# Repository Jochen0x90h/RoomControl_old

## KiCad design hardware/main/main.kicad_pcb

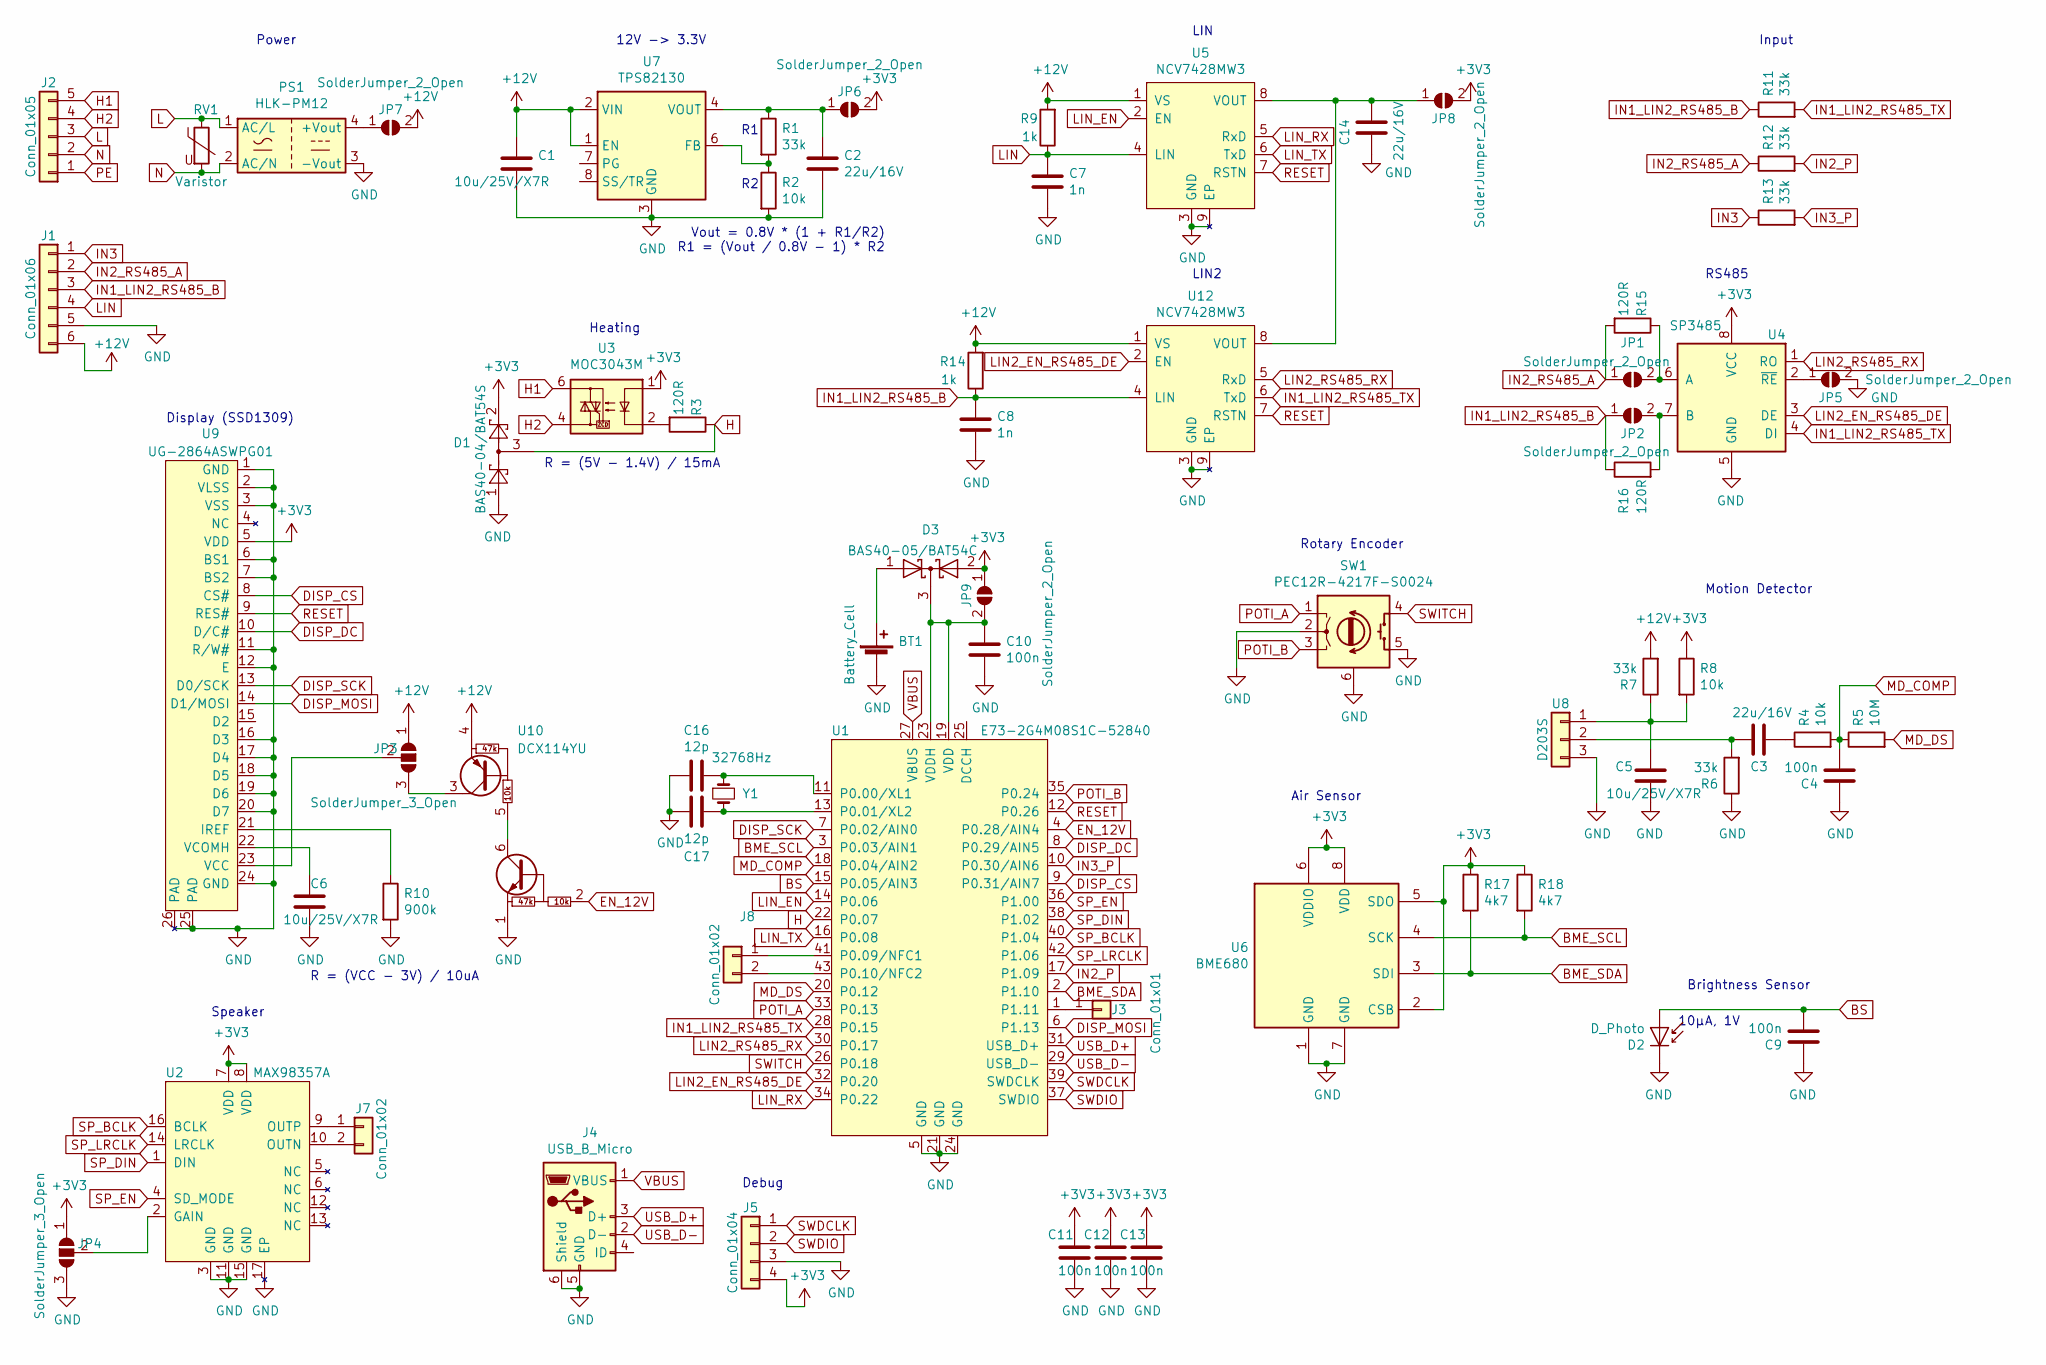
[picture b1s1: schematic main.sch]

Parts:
BT1: Battery_Cell; Battery_2032
C1, C5, C6: 10u/25V/X7R; C_1206_3216Metric
C2, C3, C14: 22u/16V; C_0805_2012Metric
C4, C9, C10, C11, C12, C13: 100n; C_0603_1608Metric
C7, C8: 1n; C_0603_1608Metric
C16, C17: 12p; C_0603_1608Metric
D1: BAS40-04/BAT54S; SOT-23
D2: D_Photo; DiodeHoles
D3: BAS40-05/BAT54C; SOT-23
J1: Conn_01x06; Wago_236-406
J2: Conn_01x05; Wago_236-405
J3: Conn_01x01; Pad
J4: USB_B_Micro; USB_Micro-B
J5: Conn_01x04; PinHeader_1x04_P2.54mm_Vertical
J7: Conn_01x02; PinHeader_1x02_P2.54mm_Vertical
J8: Conn_01x02; PinHeader_1x02_P2.00mm_Vertical
JP1, JP2, JP5, JP6, JP7, JP8, JP9: SolderJumper_2_Open; Jumper2
JP3, JP4: SolderJumper_3_Open; Jumper3
PS1: HLK-PM12; HiLink_HLK-PMxx
R1, R6, R7: 33k; R_0603_1608Metric
R2, R4, R8: 10k; R_0603_1608Metric
R3, R15, R16: 120R; R_1206_3216Metric
R5: 10M; R_0603_1608Metric
R9, R14: 1k; R_1206_3216Metric
R10: 900k; R_0603_1608Metric
R11, R12, R13: 33k; R_1206_3216Metric
R17, R18: 4k7; R_0603_1608Metric
RV1: Varistor; S10K275
SW1: PEC12R-4217F-S0024; Bourns_PEC12R
U1: E73-2G4M08S1C-52840
U2: MAX98357A; TQFN-16-1EP_3x3mm_P0.5mm_EP1.23x1.23mm
U3: MOC3043M; On_MOC3043
U4: SP3485; SOIC-8_3.9x4.9mm_P1.27mm
U5, U12: NCV7428MW3; On_NCV7428MW
U6: BME680; Bosch_BME680
U7: TPS82130; Texas_TPS82130
U8: D203S
U9: UG-2864ASWPG01; Connector-Flat-24_P0.5mm
U10: DCX114YU; SOT-363_SC-70-6
Y1: 32768Hz; Crystal_DS26_D2.0mm_L6.0mm_Vertical

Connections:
+3V3: C11.2, C12.2, C13.2, D1.2, D3.2 (A), J5.4, JP4.1 (A), JP6.2 (B), JP8.2 (B), JP9.1 (A), R8.1, R17.1, R18.1, U2.7 (VDD), U2.8 (VDD), U3.1, U4.8 (VCC), U6.2 (CSB), U6.5 (SDO), U6.6 (VDDIO), U6.8 (VDD), U9.5 (VDD)
+12V: C1.1, J1.6, JP3.1 (A), JP7.2 (B), R7.2, R9.2, R14.2, U5.1 (VS), U7.1 (EN), U7.2 (VIN), U10.4 (C2), U12.1 (VS)
BME_SCL: R18.2, U1.3 (P0.03/AIN1), U6.4 (SCK)
BME_SDA: R17.2, U1.2 (P1.10), U6.3 (SDI)
BS: C9.2, D2.2 (A), U1.15 (P0.05/AIN3)
DISP_CS: U1.9 (P0.31/AIN7), U9.8 (CS#)
DISP_DC: U1.8 (P0.29/AIN5), U9.10 (D/C#)
DISP_MOSI: U1.6 (P1.13), U9.14 (D1/MOSI)
DISP_SCK: U1.7 (P0.02/AIN0), U9.13 (D0/SCK)
EN_12V: U1.4 (P0.28/AIN4), U10.2 (B1)
GND: BT1.2 (-), C1.2, C2.2, C4.1, C5.2, C6.2, C7.2, C8.2, C9.1, C10.2, C11.1, C12.1, C13.1, C14.1, C16.2, C17.2, D1.1, D2.1 (K), J1.5, J4.5 (GND), J4.6 (Shield), J5.3, JP4.3 (B), JP5.2 (B), PS1.3 (-Vout), R2.2, R6.1, R10.2, SW1.2 (C), SW1.5 (S2), SW1.6 (SH), U1.5 (GND), U1.21 (GND), U1.24 (GND), U2.3 (GND), U2.11 (GND), U2.15 (GND), U2.17 (EP), U4.5 (GND), U5.3 (GND), U5.9 (EP), U6.1 (GND), U6.7 (GND), U7.3 (GND), U7.9 (GND), U8.3, U9.1 (GND), U9.2 (VLSS), U9.3 (VSS), U9.6 (BS1), U9.7 (BS2), U9.11 (R/W#), U9.12 (E), U9.16 (D3), U9.17 (D4), U9.18 (D5), U9.19 (D6), U9.20 (D7), U9.24 (GND), U9.25 (PAD), U9.26 (PAD), U10.1 (E1), U12.3 (GND), U12.9 (EP)
H: D1.3, R3.1, U1.22 (P0.07)
H1: J2.5, U3.6
H2: J2.4, U3.4
IN1_LIN2_RS485_B: C8.1, J1.3, JP2.1 (A), R11.1, R14.1, R16.1, U12.4 (LIN)
IN1_LIN2_RS485_TX: R11.2, U1.28 (P0.15), U4.4 (DI), U12.6 (TxD)
IN2_P: R12.2, U1.17 (P1.09)
IN2_RS485_A: J1.2, JP1.1 (A), R12.1, R15.2
IN3: J1.1, R13.1
IN3_P: R13.2, U1.10 (P0.30/AIN6)
L: J2.3, PS1.1 (AC/L), RV1.1
LIN: C7.1, J1.4, R9.1, U5.4 (LIN)
LIN2_EN_RS485_DE: U1.32 (P0.20), U4.3 (DE), U12.2 (EN)
LIN2_RS485_RX: U1.30 (P0.17), U4.1 (RO), U12.5 (RxD)
LIN_EN: U1.14 (P0.06), U5.2 (EN)
LIN_RX: U1.34 (P0.22), U5.5 (RxD)
LIN_TX: U1.16 (P0.08), U5.6 (TxD)
MD_COMP: C4.2, R4.2, R5.1, U1.18 (P0.04/AIN2)
MD_DS: R5.2, U1.20 (P0.12)
N: J2.2, PS1.2 (AC/N), RV1.2
unnamed: BT1.1 (+), D3.1 (A)
unnamed: C2.1, JP6.1 (A), R1.1, U7.4 (VOUT), U7.5 (VOUT)
unnamed: C3.1, R4.1
unnamed: C3.2, R6.2, U8.2
unnamed: C5.1, R7.1, R8.2, U8.1
unnamed: C6.1, U9.22 (VCOMH)
unnamed: C10.1, D3.3 (K), JP9.2 (B), U1.19 (VDD), U1.23 (VDDH)
unnamed: C14.2, JP8.1 (A), U5.8 (VOUT), U12.8 (VOUT)
unnamed: C16.1, U1.11 (P0.00/XL1), Y1.1
unnamed: C17.1, U1.13 (P0.01/XL2), Y1.2
unnamed: J3.1, U1.1 (P1.11)
unnamed: J7.1, U2.9 (OUTP)
unnamed: J7.2, U2.10 (OUTN)
unnamed: J8.1, U1.41 (P0.09/NFC1)
unnamed: J8.2, U1.43 (P0.10/NFC2)
unnamed: JP1.2 (B), R15.1, U4.6 (A)
unnamed: JP2.2 (B), R16.2, U4.7 (B)
unnamed: JP3.2 (C), U9.23 (VCC)
unnamed: JP3.3 (B), U10.3 (C2)
unnamed: JP4.2 (C), U2.2 (GAIN)
unnamed: JP5.1 (A), U4.2 (~RE~)
unnamed: JP7.1 (A), PS1.4 (+Vout)
unnamed: R1.2, R2.1, U7.6 (FB)
unnamed: R3.2, U3.2
unnamed: R10.1, U9.21 (IREF)
unnamed: U10.5 (B2), U10.6 (C1)
PE: J2.1
POTI_A: SW1.1 (A), U1.33 (P0.13)
POTI_B: SW1.3 (B), U1.35 (P0.24)
RESET: U1.12 (P0.26), U5.7 (RSTN), U9.9 (RES#), U12.7 (RSTN)
SP_BCLK: U1.40 (P1.04), U2.16 (BCLK)
SP_DIN: U1.38 (P1.02), U2.1 (DIN)
SP_EN: U1.36 (P1.00), U2.4 (SD_MODE)
SP_LRCLK: U1.42 (P1.06), U2.14 (LRCLK)
SWDCLK: J5.1, U1.39 (SWDCLK)
SWDIO: J5.2, U1.37 (SWDIO)
SWITCH: SW1.4 (S1), U1.26 (P0.18)
USB_D+: J4.3 (D+), U1.31 (USB_D+)
USB_D-: J4.2 (D-), U1.29 (USB_D-)
VBUS: J4.1 (VBUS), U1.27 (VBUS)

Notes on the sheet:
Vout = 0.8V * (1 + R1/R2) R1 = (Vout / 0.8V - 1) * R2
R = (VCC - 3V) / 10uA
Motion Detector
Display (SSD1309)
Speaker
Brightness Sensor
Input
LIN
RS485
12V -> 3.3V
Rotary Encoder
Air Sensor
Power
Heating
10µA, 1V
R = (5V - 1.4V) / 15mA
LIN2
Debug

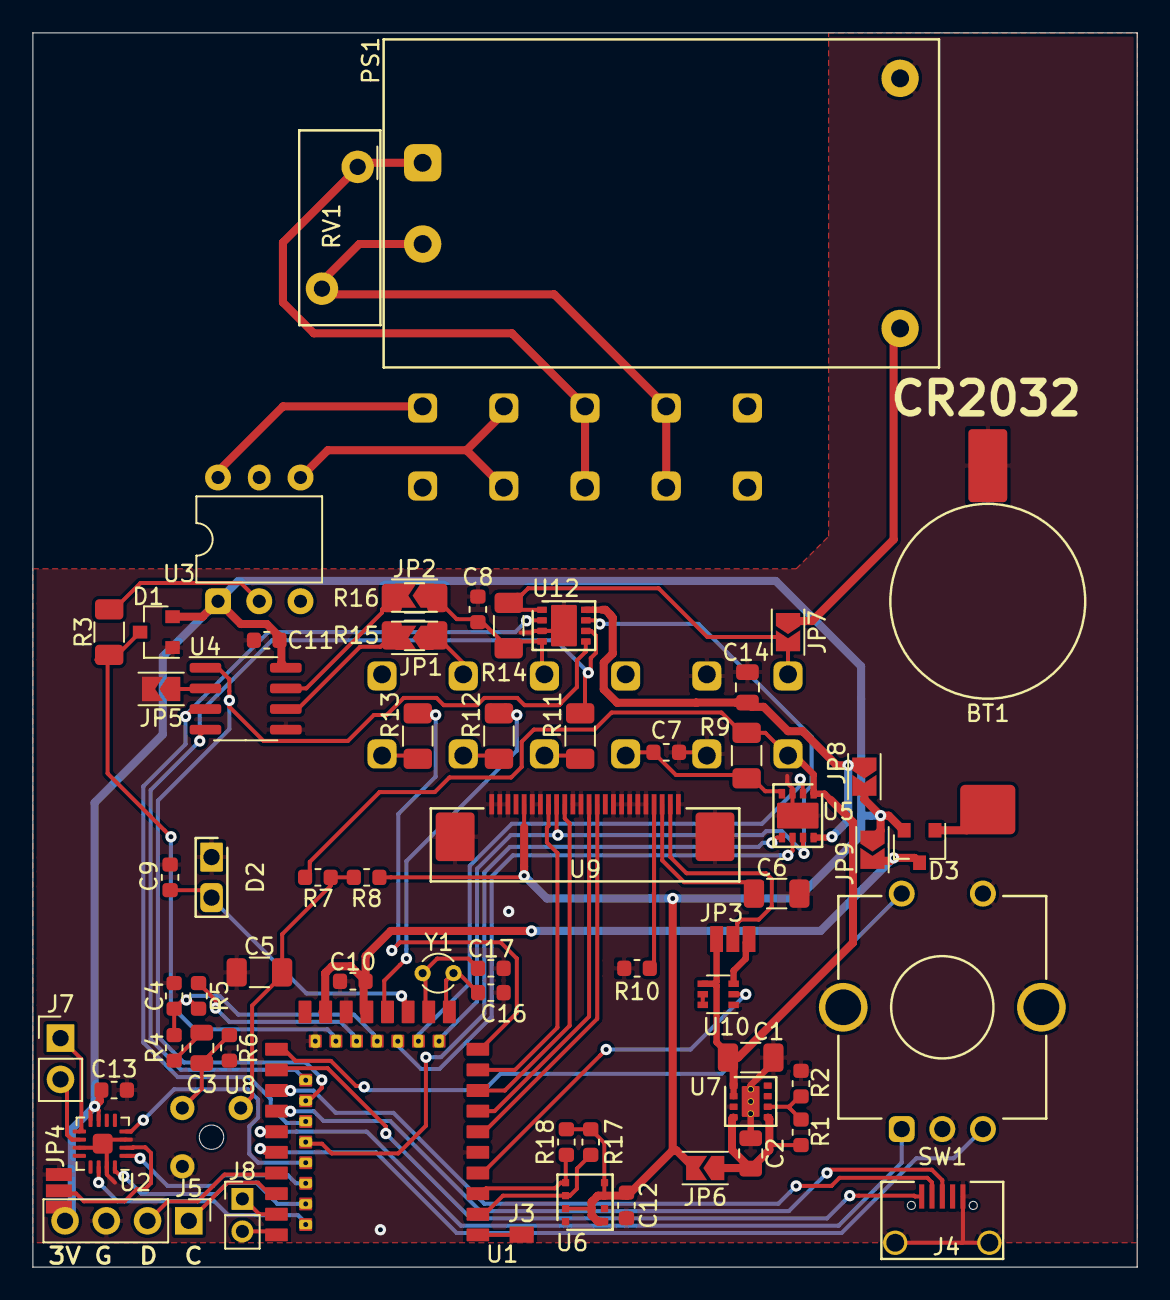
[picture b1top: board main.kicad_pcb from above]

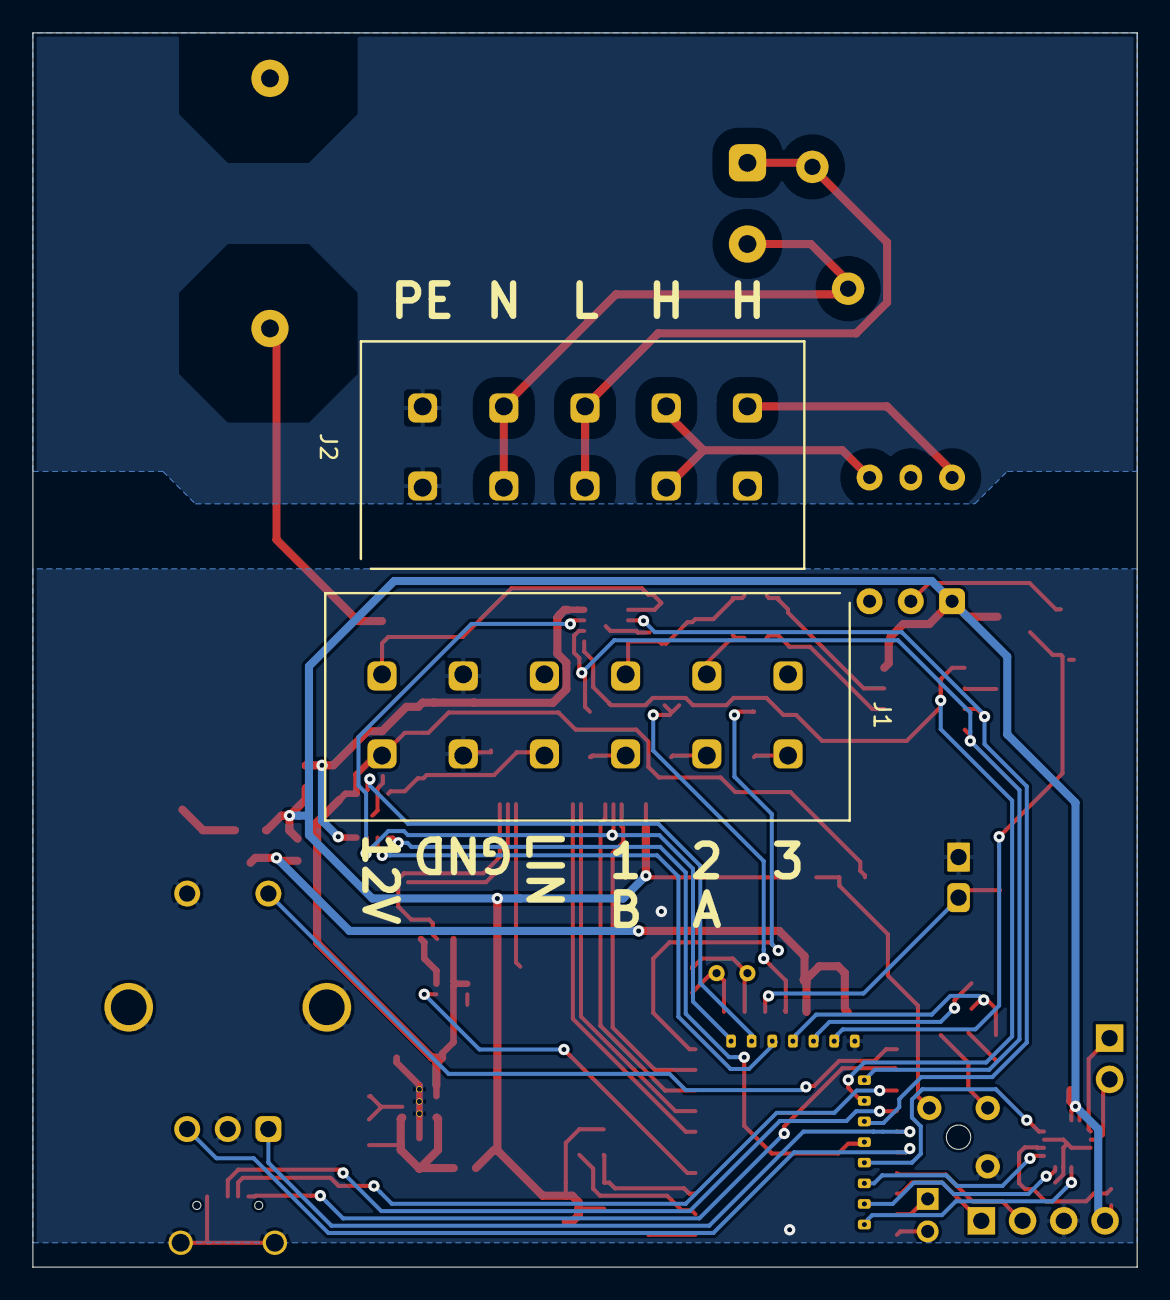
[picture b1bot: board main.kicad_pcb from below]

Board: 2 copper layers, 68.0 x 76.0 mm, 69 parts (2 on the bottom side), 69 nets.

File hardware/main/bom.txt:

1 120R 1206
1 1k 1206
3 10k 0603
3 33k 0603
1 900k 0603
1 10M 0603
2 12p 0603
7 100n 0603
3 10u/25V/X7R 1206
3 22u/16V 0805
1 E73-2G4M08S1C-52840
1 NCV7428MW3 (On lin driver)
1 MOC3043M (On optotriac)
1 MAX98357A (Maxim audio driver)
1 BME680 (Bosch air sensor)
1 PEC12R-4217F-S0024 (Bourns poti)
1 IRA-S410ST01 (Murata pir sensor)
1 IML-0685 (lens)
1 SFH 203 P (Osram photodiode)
1 BAS40-05/BAT54C
1 CR2032 holder
1 32768Hz (crystal)
1 S10K275 (varistor)
1 Wago 236-405
1 Wago 236-406
1 USB_B_Micro
1 24 pin display connector
1 TPS82130 (Texas buck converter 17V)
1 HLK-PM12 (AC/DC converter)
1 CDS-25148-L100 (Cui Devices speaker)

[inputs]
3 33k 1206

[ledstrip]
2 120R 1206
1 SP3485 (rs485 driver)
1 100n 0603

[optional]
1 1k 1206
2 4k7 0603
1 DCX114YU
1 BAS40-04/BAT54S
1 NCV7428MW3 (On lin driver)

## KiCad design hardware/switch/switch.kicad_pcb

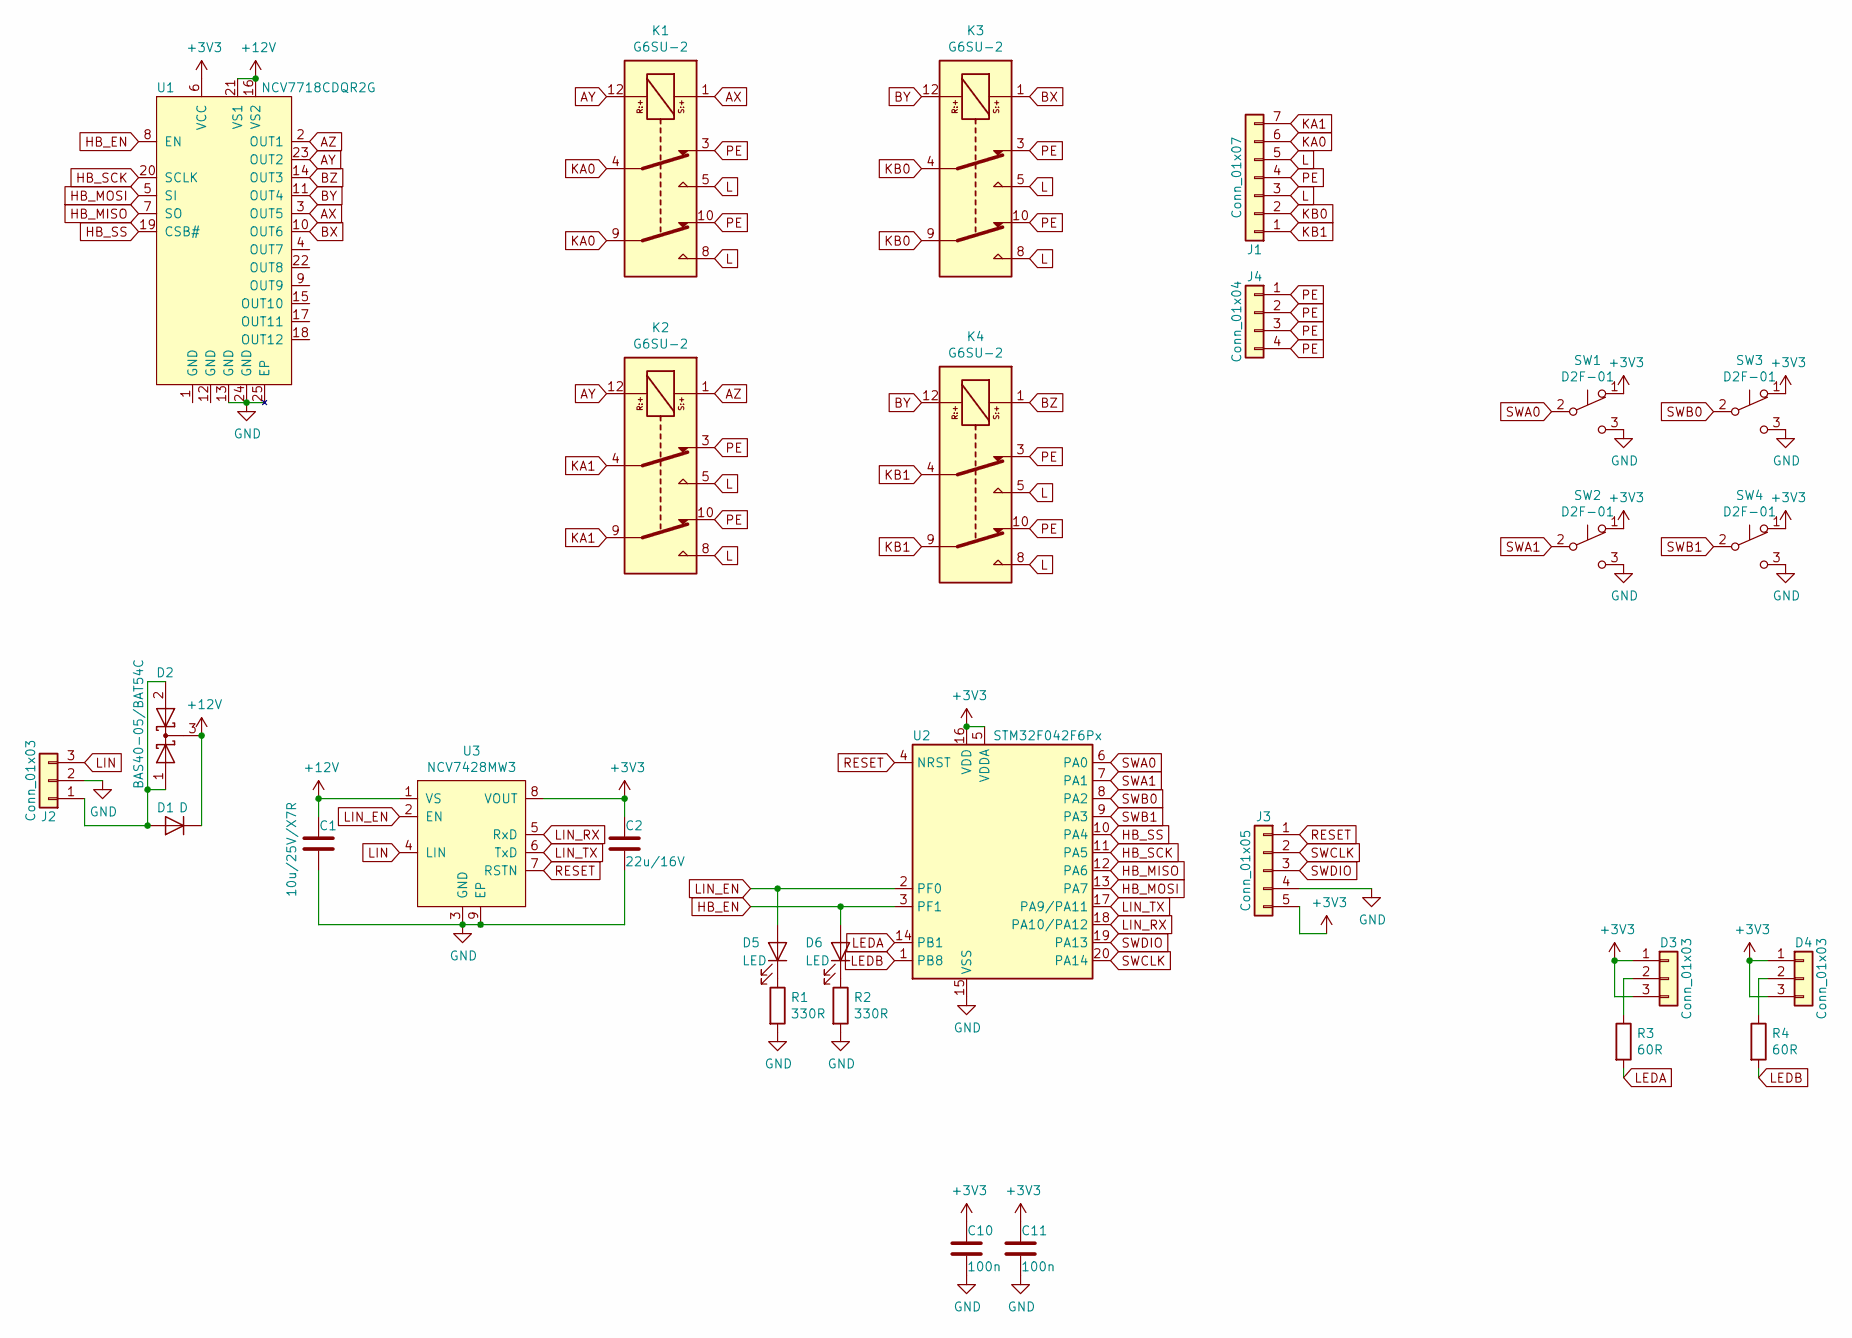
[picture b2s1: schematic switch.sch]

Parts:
C1: 10u/25V/X7R; C_1206_3216Metric
C2: 22u/16V; C_0805_2012Metric
C10, C11: 100n; C_0603_1608Metric
D1: D; D_1206_3216Metric_Castellated
D2: BAS40-05/BAT54C; SOT-23
D3, D4: Conn_01x03; DiodeHoles3
D5, D6: LED; LED_0805_2012Metric_Castellated
J1: Conn_01x07; Wago_236-407
J2: Conn_01x03; Wago_236-403
J3: Conn_01x05; PinHeader_1x05_P2.54mm_Vertical
J4: Conn_01x04; Switch_Mount
K1, K2, K3, K4: G6SU-2; Omron_G6SU-2
R1, R2: 330R; R_0603_1608Metric
R3, R4: 60R; R_0603_1608Metric
SW1, SW2, SW3, SW4: D2F-01; Omron_D2F-01
U1: NCV7718CDQR2G; On_NCV77xx
U2: STM32F042F6Px; STM32F042F6
U3: NCV7428MW3; On_NCV7428MW

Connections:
+3V3: C2.1, C10.1, C11.1, D3.1, D3.3, D4.1, D4.3, J3.5, SW1.1 (A), SW2.1 (A), SW3.1 (A), SW4.1 (A), U1.6 (VCC), U2.5 (VDDA), U2.16 (VDD), U3.8 (VOUT)
+12V: C1.1, D1.1 (K), D2.3 (K), U1.16 (VS2), U1.21 (VS1), U3.1 (VS)
AX: K1.1, U1.3 (OUT5)
AY: K1.12, K2.12, U1.23 (OUT2)
AZ: K2.1, U1.2 (OUT1)
BX: K3.1, U1.10 (OUT6)
BY: K3.12, K4.12, U1.11 (OUT4)
BZ: K4.1, U1.14 (OUT3)
GND: C1.2, C2.2, C10.2, C11.2, J2.2, J3.4, R1.2, R2.2, SW1.3 (C), SW2.3 (C), SW3.3 (C), SW4.3 (C), U1.13 (GND), U1.24 (GND), U1.25 (EP), U2.15 (VSS), U3.3 (GND), U3.9 (EP)
HB_EN: D6.2 (A), U1.8 (EN), U2.3 (PF1)
HB_MISO: U1.7 (SO), U2.12 (PA6)
HB_MOSI: U1.5 (SI), U2.13 (PA7)
HB_SCK: U1.20 (SCLK), U2.11 (PA5)
HB_SS: U1.19 (CSB#), U2.10 (PA4)
KA0: J1.6, K1.4, K1.9
KA1: J1.7, K2.4, K2.9
KB0: J1.2, K3.4, K3.9
KB1: J1.1, K4.4, K4.9
L: J1.3, J1.5, K1.5, K1.8, K2.5, K2.8, K3.5, K3.8, K4.5, K4.8
LEDA: R3.2, U2.14 (PB1)
LEDB: R4.2, U2.1 (PB8)
LIN: J2.3, U3.4 (LIN)
LIN_EN: D5.2 (A), U2.2 (PF0), U3.2 (EN)
LIN_RX: U2.18 (PA10/PA12), U3.5 (RxD)
LIN_TX: U2.17 (PA9/PA11), U3.6 (TxD)
unnamed: D1.2 (A), D2.1 (A), D2.2 (A), J2.1
unnamed: D3.2, R3.1
unnamed: D4.2, R4.1
unnamed: D5.1 (K), R1.1
unnamed: D6.1 (K), R2.1
PE: J1.4, J4.1, J4.2, J4.3, J4.4, K1.3, K1.10, K2.3, K2.10, K3.3, K3.10, K4.3, K4.10
RESET: J3.1, U2.4 (NRST), U3.7 (RSTN)
SWA0: SW1.2 (B), U2.6 (PA0)
SWA1: SW2.2 (B), U2.7 (PA1)
SWB0: SW3.2 (B), U2.8 (PA2)
SWB1: SW4.2 (B), U2.9 (PA3)
SWCLK: J3.2, U2.20 (PA14)
SWDIO: J3.3, U2.19 (PA13)

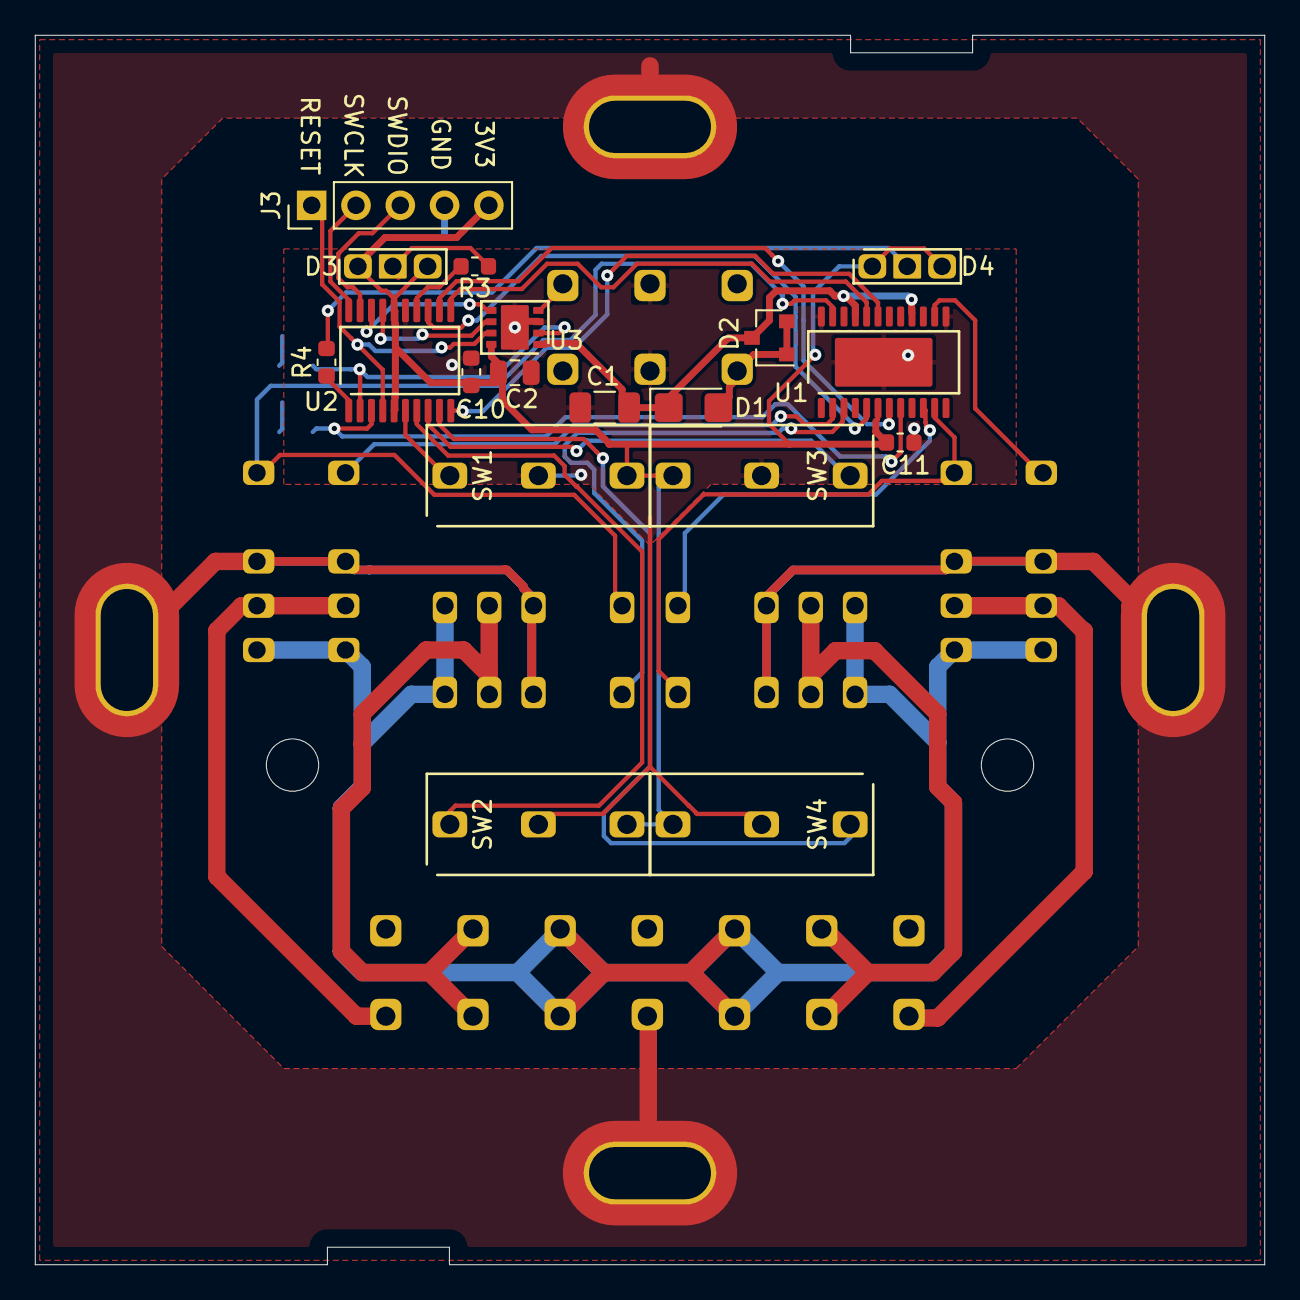
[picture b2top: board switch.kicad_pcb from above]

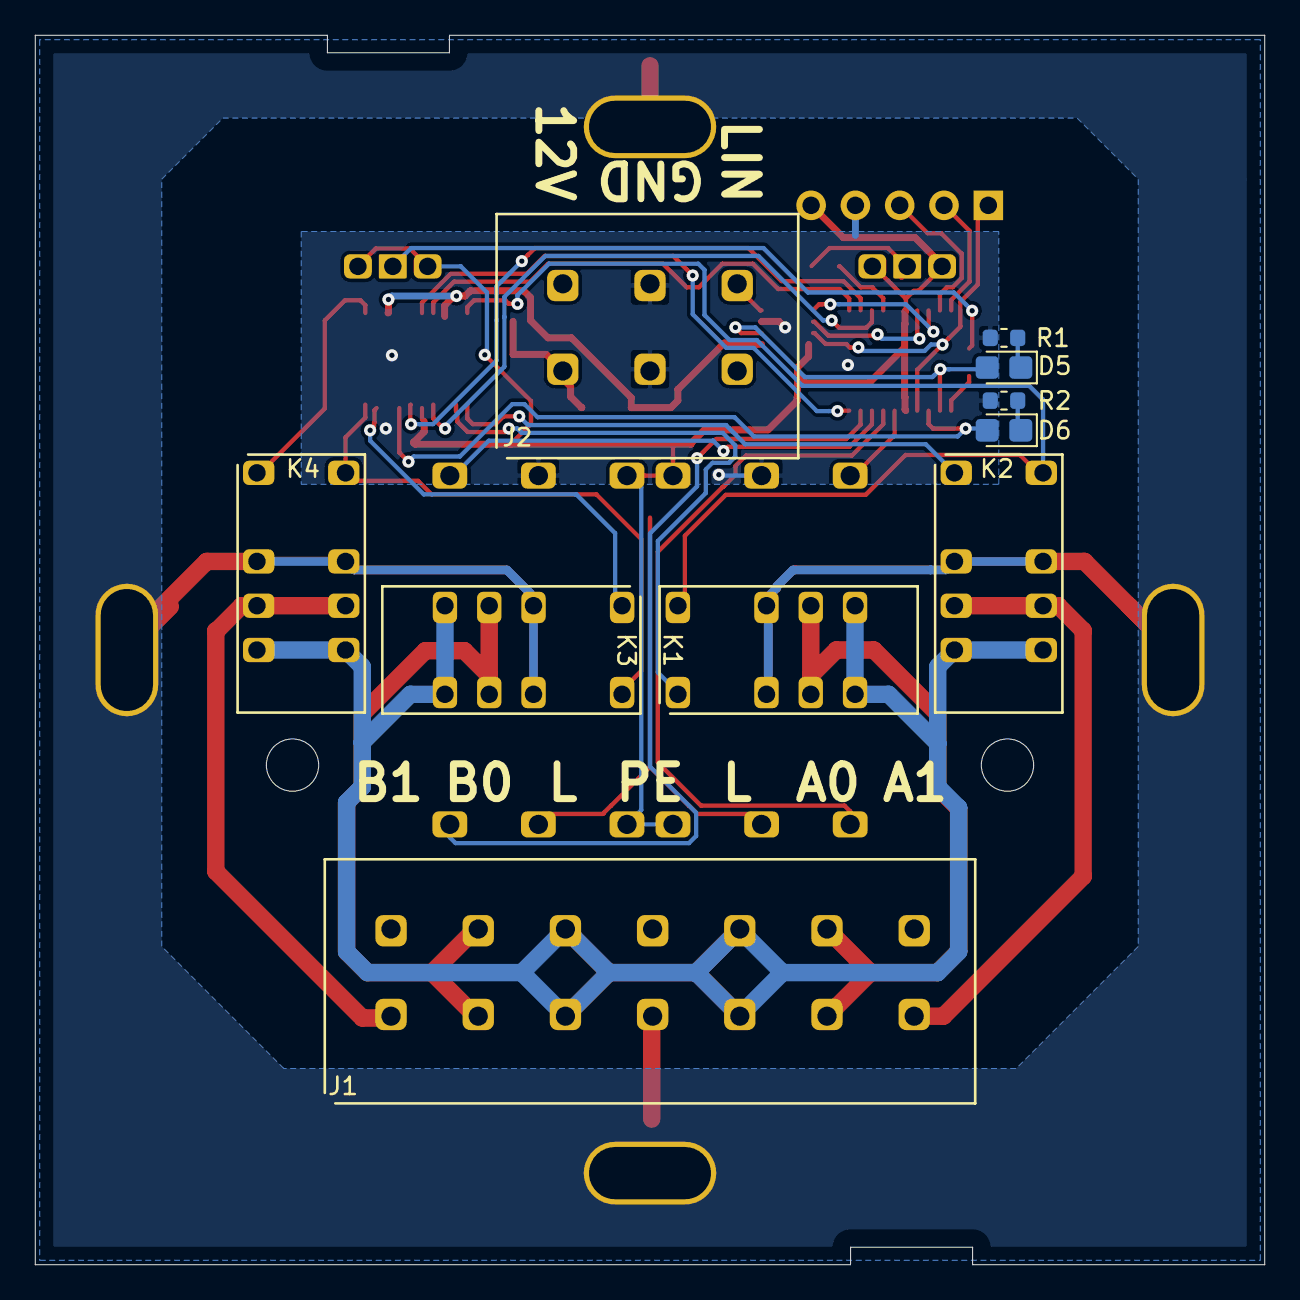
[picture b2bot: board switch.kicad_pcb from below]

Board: 2 copper layers, 70.5 x 70.5 mm, 29 parts (10 on the bottom side), 38 nets.

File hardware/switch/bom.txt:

2 100n 0603
1 10u/25V/X7R 1206
1 22u/16V 0805
1 STM32F042F6
1 NCV7718 (On relay driver)
1 NCV7428MW3 (On lin driver)
1 BAS40-05/BAT54C
4 D2F-01 (Omron switch)
4 G6SU-2 (Omron relay)
1 Wago 236-403
1 Wago 236-407

[optional]
2 330R 0603
2 LED 0805
1 Diode 1206
2 PLW5-3MM (Bivar lightpipe)

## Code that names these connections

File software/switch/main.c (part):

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int const SWITCH_PINS = 0xf; // port A

// lin driver
int const LIN_RX_PIN = 0x400; // port A
int const LIN_EN_PIN = 1; // port F
int const LIN_TIMER_FREQUENCY = 1000; // 1kHz
int const LIN_SLEEP_TIMEOUT = 1; // 1ms
int const LIN_IDLE_TIMEOUT = 4000; // 4s
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}

void clearPinInterrupts() {
	EXTI->PR = LIN_RX_PIN | SWITCH_PINS;
	NVIC->ICPR[0] = (1 << EXTI0_1_IRQn) | (1 << EXTI2_3_IRQn) | (1 << EXTI4_15_IRQn);
}

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
void enableLin() {
	// set driver pin high
	GPIOF->BSRR = LIN_EN_PIN;

	// enable peripheral clock
	RCC->APB2ENR |= RCC_APB2ENR_USART1EN | RCC_APB2ENR_TIM1EN;
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
void disableLin() {
	// set driver pin low
	GPIOF->BRR = LIN_EN_PIN;

	// usart
	USART1->CR1 &= ~USART_CR1_UE;
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	// configure GPIOs
	// see chapter 8.4 in reference manual
	
	// preserve SW-DP on PA13 and PA14
	// GPIOA          PA0 SWA0 | PA1 SWA1 | PA2 SWB0 | PA3 SWB1 | PA4 NSS  | PA5 SCK  | PA6 MISO | PA7 MOSI | PA9 TX   | PA10 RX
	GPIOA->MODER   |= IN(0)    | IN(1)    | IN(2)    | IN(3)    | ALT(4)   | ALT(5)   | ALT(6)   | ALT(7)   | ALT(9)   | ALT(10);
	GPIOA->OSPEEDR |=                                             HI(4)    | HI(5)    | HI(6)    | HI(7)    | HI(9)    | HI(10);
	GPIOA->PUPDR   |= UP(0)    | UP(1)    | UP(2)    | UP(3)    | OFF(4)   | OFF(5)   | UP(6)    | OFF(7)   | OFF(9)   | UP(10);
	GPIOA->AFR[0]  |=                                             AF(4, 0) | AF(5, 0) | AF(6, 0) | AF(7, 0);
	GPIOA->AFR[1]  |=                                                                                         AF(9, 1) | AF(10, 1);

	// GPIOB       PB1 JPA | PB8 JPB
	GPIOB->MODER = IN(1)   | IN(8);
	GPIOB->PUPDR = UP(1)   | UP(8);

	// GPIOF         PF0 LIN_EN | PF1 RD_EN
	GPIOF->MODER   = OUT(0)     | OUT(1);
	GPIOF->OSPEEDR = HI(0)      | HI(1);

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	bool jpb = (GPIOB->IDR & 8) == 0;
	
	// switch off port B again
	// GPIOB       PB1 JPA | PB8 JPB
	GPIOB->MODER = AN(1)   | AN(8);
	GPIOB->PUPDR = OFF(1)  | OFF(8);
	RCC->AHBENR = RCC_AHBENR_GPIOAEN | RCC_AHBENR_GPIOFEN;
	

	// enable interrupts for switches on PA0 - PA3 and LIN_RX on PA10
	// see chapter 11.2 in reference manual and A.6.2 for code example
	SYSCFG->EXTICR[0] = SYSCFG_EXTICR1_EXTI0_PA | SYSCFG_EXTICR1_EXTI1_PA | SYSCFG_EXTICR1_EXTI2_PA | SYSCFG_EXTICR1_EXTI3_PA;
	EXTI->FTSR = LIN_RX_PIN | SWITCH_PINS; // detect falling edge for lin and switches
	EXTI->RTSR = SWITCH_PINS; // detect rising edge for switches
	
	// USART for LIN
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	uint8_t relays = 0;
	uint8_t relayState = 0xf0; // force initial set of relays

	// enable pin interrupts to detect LIN activity and switch state changes
	EXTI->IMR = LIN_RX_PIN | SWITCH_PINS;
	
	int countA;
	int countB
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				// no: start switch timer
				startSwitchTimer();
				
				// only disable switch pin interrupts
				EXTI->IMR &= ~SWITCH_PINS;
			} else {
				// yes: wake up LIN by sending low pulse
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		case SLEEP:
			{
				// check for LIN wakeup
				if ((EXTI->PR & LIN_RX_PIN) != 0) {
					// enable up LIN
					enableLin();
					linState = AWAKE;
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		if ((TIM1->SR & TIM_SR_UIF) != 0) {
			frameState = IDLE;

			// enable pin interrupts to detect lin activity switch state changes
			EXTI->IMR = LIN_RX_PIN | SWITCH_PINS;

			// go to sleep mode if switches haven't changed since last read
			if (switches == (~GPIOA->IDR & SWITCH_PINS) || switchesId == -1) {
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
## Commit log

2019-08-15 Simulation of actors for lights and blinds
2019-09-16 Add menus for buttons and scenarios and flash emulator
2019-10-15 Add timers and temperature control
2019-11-10 Switch to device (state machine) concept
2019-11-23 Add motion sensor to emulator
2019-12-15 New menu and storage paradigms
2019-12-20 Add file structure for stm32f0
2020-03-07 Add MQTT-SN client
2020-05-16 Add Hardware
2020-05-17 Add openscad models for box and switch
2020-05-27 Refactoring user interface of emulator
2020-05-29 Add pcb for switch
2020-06-13 Use LIN instead of CAN transciever
2020-07-08 add software for switch
2020-07-19 Update main board to use LIN
2020-08-07 Add backup battery and 32768Hz crystal
2020-08-20 New speaker and pir sensor lens
2020-09-15 Add indicator LEDs to switch
2020-09-20 Add MQTT-SN broker
2020-09-27 Add local devices based on lin and mqtt
2020-10-04 Timing for relays and blind
2020-10-08 Add float to string conversions and optional
2020-10-13 Own SystemTime class and using conan
2020-10-18 State handling for switch and blind
2020-10-19 Unified Network class
2020-11-30 Topic selector menu
2020-12-04 Add routes
2020-12-26 New bus device
2020-12-29 refactored route and timer
